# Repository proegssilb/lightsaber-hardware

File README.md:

# lightsaber-hardware
Kicad projects and other files for lightsaber soundboard hardware.

## Caveat Emptor
NO WARRANTY IS AVAILABLE, EXPRESSLY STATED, OR IMPLIED.

These designs and files are not guaranteed to have been reviewed by a professional
engineer. They are not guaranteed to work in your design. They are not even 
guaranteed to work if sent to a PCB manufacturer. The author(s) cannot be held
liable for any injuries or damage that occurs as a result of using these files. It
is your responsibility to review all designs and files carefully before using them 
or integrating them into your own design.

Let the buyer beware.

## Licensing
See the LICENSE.txt file. It's a CERN-OHL-S-2.0 license. If that doesn't work for you,
let's talk.

## Structure
Each subfolder represents a different kicad project, each attempting a different board, 
either in terms of features or formfactor.

Documentation, if any is available, will be either a README in each design's root, or a
`docs/` folder in each design.

## Tool Versions
I use the latest kicad version from flatpak. If you can't open a project, feel free to 
file an issue, but there's a limit to how much support I can provide.

## 3rd Party Services
Preferred PCB manufacturers include JLCBCP, OSH Park, and PCBWay, but any given project 
won't necessarily support all 3 manufacturers. Preferred distributors include Digikey,
Mouser, and LCSC. Same caveat with preferred PCB Manufacturers applies to distributors.

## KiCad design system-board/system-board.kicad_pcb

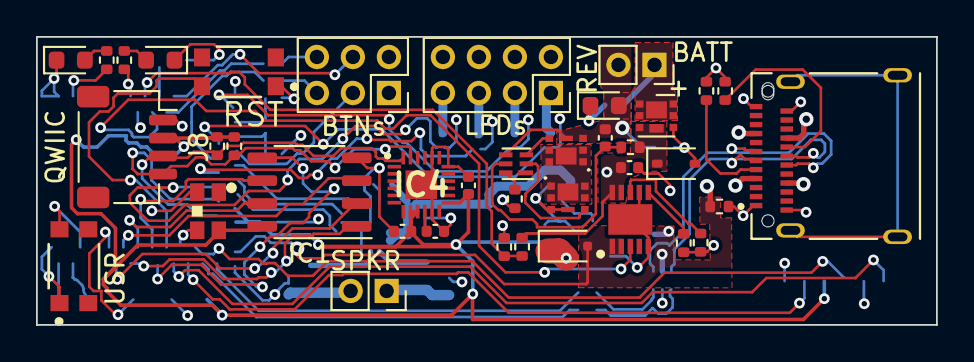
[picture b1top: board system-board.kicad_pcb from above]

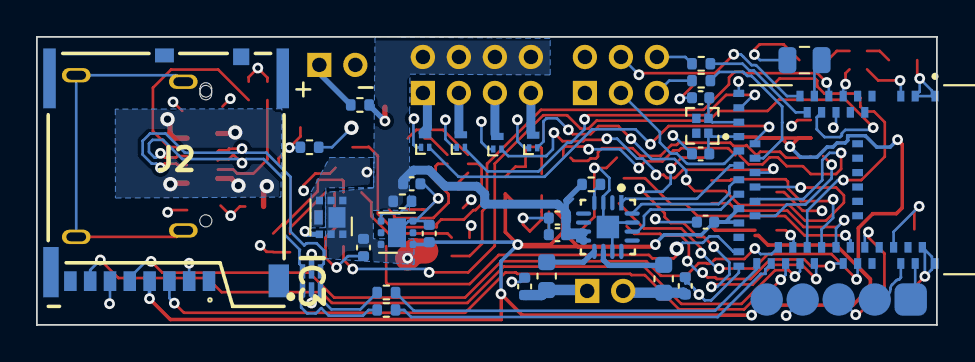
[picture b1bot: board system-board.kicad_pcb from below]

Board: 4 copper layers, 50.0 x 16.0 mm, 72 parts (33 on the bottom side), 74 nets.

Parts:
C1, C7, C9, C13: 10u; C_0402_1005Metric
C2, C3: 22p; C_0402_1005Metric
C4: 0.1 uF; C_0805_2012Metric
C5, C6: 220p; C_0402_1005Metric
C8: 100 nF; C_0402_1005Metric
C10, C14, C15, C16: 0.1 uF; C_0402_1005Metric
C11, C12: 4.7u; C_0402_1005Metric
D1: WS2812B-2020
D2: BLUE; LED_0603_1608Metric
D3: RED; LED_0603_1608Metric
D4: BZX38450; D_SOD-323
D5: REV; LED_0603_1608Metric
D6: PMEG1030EJ; D_SOD-323F
FB1, FB2: FB_Sm; C_0603_1608Metric
IC1: Flash_16Mb; SOP-8_3.9x4.9mm_P1.27mm
IC2: MCP73834T-FCI_MF; SON50P300X300X100-11N-D
IC3: HSP061-2M6; SON50P100X145X65-6N-D
IC4: ICM-20648; QFN40P300X300X95-25N-D
J1: BATT; PinSocket_1x02_P2.00mm_Vertical
J2: 503398-1892; Molex uSD Card Holder Push-Push 503398-1892
J3: DBG; Prog-Pads
J4: SPKR; PinSocket_1x02_P2.00mm_Vertical
J5: LEDs; PinSocket_2x04_P2.00mm_Vertical
J6: BTNs; PinSocket_2x03_P2.00mm_Vertical
J7: 105450-0101; AMPHENOL_12401832E402A
J8: QWIIC; JST_SH_SM04B-SRSS-TB_1x04-1MP_P1.00mm_Horizontal
Q1, Q4: DMP1012UFDF
Q2, Q3: SSM6K504NU.LF; SSM6K504NULF
Q5, Q6, Q7, Q8: PMZB290UNE2YL; Diodes_DFN1006-3
R1, R2: 22; R_0402_1005Metric
R3, R4, R10, R16, R17: 1k; R_0402_1005Metric
R5: 1M; R_0402_1005Metric
R6: 330; R_0402_1005Metric
R7: 2.2k; R_0402_1005Metric
R8, R20, R21: 2.0k; R_0402_1005Metric
R9: 10k; R_0402_1005Metric
R11: 200; R_0402_1005Metric
R12, R13, R14, R15: 100k; R_0402_1005Metric
R18, R19: 5k1; R_0402_1005Metric
SW1: RST; CK_Components-KMR231NG_LFS-MFG
SW2: USR; CK_Components-KMR231NG_LFS-MFG
U1: MDBT50Q-1MV2; XCVR_MDBT50Q-1MV2
U2: MAX98357AETE+T; Maxim_Integrated-T1633-4-0-V-IPC_C
U3: BQ29705DSER; WSON-6_1.5x1.5mm_P0.5mm
U4: TLV75733PDRV; WSON-6-1EP_2x2mm_P0.65mm_EP1x1.6mm
Y1: 32.768k; XTAL_ECS-.327-12.5-1210B-N-TR

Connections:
/A0: J6.3, U1.20 (P0.04/AIN2)
/A1: R17.2, U1.21 (P0.05/AIN3)
/A2: J6.4, U1.14 (P0.30/AIN6)
/A3: R16.2, U1.13 (P0.28/AIN4)
/A4: IC2.3 (STAT1), U1.11 (P0.02/AIN0)
/AREF: C4.2, U1.12 (P0.31/AIN7)
/Blade LED Out/Blade_1_Out: J5.1, Q5.3 (S)
/Blade LED Out/Blade_2_Out: J5.3, Q6.3 (S)
/Blade LED Out/Blade_3_Out: J5.5, Q7.3 (S)
/Blade LED Out/Blade_4_Out: J5.7, Q8.3 (S)
/CONN_USB_D+: IC3.1 (I/O1_1), R2.1
/CONN_USB_D-: IC3.3 (I/O2_1), R1.1
/D5: Q8.2 (G), U1.25 (P1.08)
/D6: Q7.2 (G), U1.23 (TRACECLK/P0.07)
/D9: Q5.2 (G), U1.19 (P0.26)
/D10: Q6.2 (G), U1.16 (P0.27)
/D11: U1.22 (P0.06), U2.1 (DIN)
/D12: U1.24 (P0.08), U2.16 (BCLK)
/D13: U1.26 (TRACEDATA3/P1.09), U2.14 (LRCLK)
/LED1: R4.2, U1.8 (P1.15)
/LED2: R3.2, U1.3 (P1.10)
/MCU_USB_D+: R2.2, U1.35 (D+)
/MCU_USB_D-: R1.2, U1.34 (D-)
/MISO: J2.7 (DAT0), U1.39 (P0.15)
/MOSI: J2.3 (CMD), U1.37 (P0.13)
/NEOPIX: D1.3 (DIN), U1.38 (P0.16)
/Power Management/BATT_FILTERED: C10.1, R6.2, U3.5 (BAT)
/Power Management/BATT_PROT_+: C9.1, D4.1 (K), IC2.9 (VBAT_1), IC2.10 (VBAT_2), Q1.3 (S), Q4.3 (S), R6.1, R12.1
/Power Management/BATT_RAW_+: J1.1, Q1.1 (D), R10.1
/Power Management/BATT_RAW_-: C10.2, D5.2 (A), J1.2, Q3.3 (S), R11.2, U3.4 (VSS)
/Power Management/VBUS: D6.2 (A), IC2.1 (VDD_1), IC2.2 (VDD_2), IC3.5 (VBUS), J7.A4 (VBUS_A), J7.A9 (VBUS_A), J7.B4 (VBUS_B), J7.B9 (VBUS_B), Q4.2 (G), R14.1, U1.32 (VBUS)
/QSPI_CS: IC1.1 (CS#), U1.44 (P0.20)
/QSPI_D0: IC1.5 (SI_(IO0)), U1.41 (P0.17)
/QSPI_D1: IC1.2 (SO_(IO1)), U1.46 (P0.22)
/QSPI_D2: IC1.3 (WP#_(IO2)), U1.45 (P0.23)
/QSPI_D3: IC1.7 (HOLD#_(IO3)), U1.43 (P0.21)
/QSPI_SCK: IC1.6 (SCLK), U1.42 (P0.19)
/RESET: SW1.2, U1.40 (~RESET/P0.18)
/SCK: J2.5 (CLK), U1.36 (P0.14)
/SCL: IC4.23 (SCL_/_SCLK), J8.4, R21.1, U1.27 (TRACEDATA2/P0.11)
/SDA: IC4.24 (SDA_/_SDI), J8.3, R20.2, U1.29 (TRACEDATA1/P0.12)
/SW0: J3.3, U1.47 (TRACEDATA0/P1.00)
/SWCLK: J3.1, U1.53 (SWDCLK)
/SWDIO: J3.2, U1.51 (SWDIO)
/SWITCH: SW2.2, U1.50 (P1.02)
/USB Connector/CC1: J7.A5 (CC1), R18.1
/USB Connector/CC2: J7.B5 (CC2), R19.1
/USB Connector/RAW_D+: IC3.6 (I/O1_2), J7.A6 (D1+), J7.B6 (D2+)
/USB Connector/RAW_D-: IC3.4 (I/O2_2), J7.A7 (D1-), J7.B7 (D2-)
/VDIV: R12.2, R13.1, U1.10 (P0.29/AIN5)
/XL1: C2.1, U1.17 (XL1/P0.00), Y1.2
/XL2: C3.1, U1.18 (XL2/P0.01), Y1.1
/i2s_amp/SOUND_OUT_N: FB1.2, U2.10 (OUTN)
/i2s_amp/SOUND_OUT_P: FB2.2, U2.9 (OUTP)
/i2s_amp/SPKR_N: C5.2, FB1.1, J4.2
/i2s_amp/SPKR_P: C6.2, FB2.1, J4.1
GND: C1.1, C2.2, C3.2, C4.1, C5.1, C6.1, C7.1, C8.2, C9.2, C11.2, C12.2, C13.2, C14.1, C15.2, C16.2, D1.2 (VSS), D2.1 (K), D3.1 (K), IC1.4 (VSS), IC2.5 (VSS), IC2.7 (~PG_(TE)), IC2.11 (EP), IC3.2 (GND), IC4.11 (FSYNC), IC4.18 (GND), IC4.20 (RESV), IC4.25 (EP), J2.2 (CD/DAT3), J2.6 (VSS), J3.4, J6.1, J6.2, J7.A1 (GND_A), J7.A12 (GND_A), J7.B1 (GND_B), J7.B12 (GND_B), J8.1, Q2.3 (S), Q5.1 (D), Q6.1 (D), Q7.1 (D), Q8.1 (D), R7.2, R8.2, R9.2, R13.2, R14.2, R18.2, R19.2, SW1.1, SW2.1, U1.1 (GND), U1.2 (GND), U1.9 (P0.03/AIN1), U1.15 (GND), U1.33 (GND), U1.54 (P0.10/NFC2), U1.55 (GND), U2.3 (GND), U2.11 (GND), U2.15 (GND), U2.17 (EP), U4.3 (GND), U4.7 (GND)
unnamed: D2.2 (A), R3.1
unnamed: D3.2 (A), R4.1
unnamed: D4.2 (A), Q1.2 (G), R11.1
unnamed: D5.1 (K), R10.2
unnamed: IC2.6 (PROG), R8.1
unnamed: IC2.8 (THERM), R9.1
unnamed: C15.1, IC4.10 (REGOUT)
unnamed: J6.5, R17.1
unnamed: J6.6, R16.1
unnamed: Q2.1 (D), Q3.1 (D)
unnamed: Q2.2 (G), U3.2 (Cout)
unnamed: Q3.2 (G), U3.3 (Dout)
unnamed: R5.1, U2.4 (~SD_MODE)
unnamed: R7.1, U3.6 (V-)
unnamed: R15.1, U4.4 (EN)
VCC: C1.2, C12.1, C14.2, C16.1, D1.4 (VDD), IC1.8 (VCC), IC4.8 (VDDIO), IC4.9 (SDO_/_AD0), IC4.13 (VDD), J2.4 (VDD), J3.5, J8.2, R20.1, R21.2, U1.28 (VDD), U1.30 (VDDH), U4.1 (OUT)
VDD: C7.2, C8.1, C11.1, C13.1, D6.1 (K), J5.2, J5.4, J5.6, J5.8, Q4.1 (D), R5.2, R15.2, U2.7 (VDD), U2.8 (VDD), U4.6 (IN)

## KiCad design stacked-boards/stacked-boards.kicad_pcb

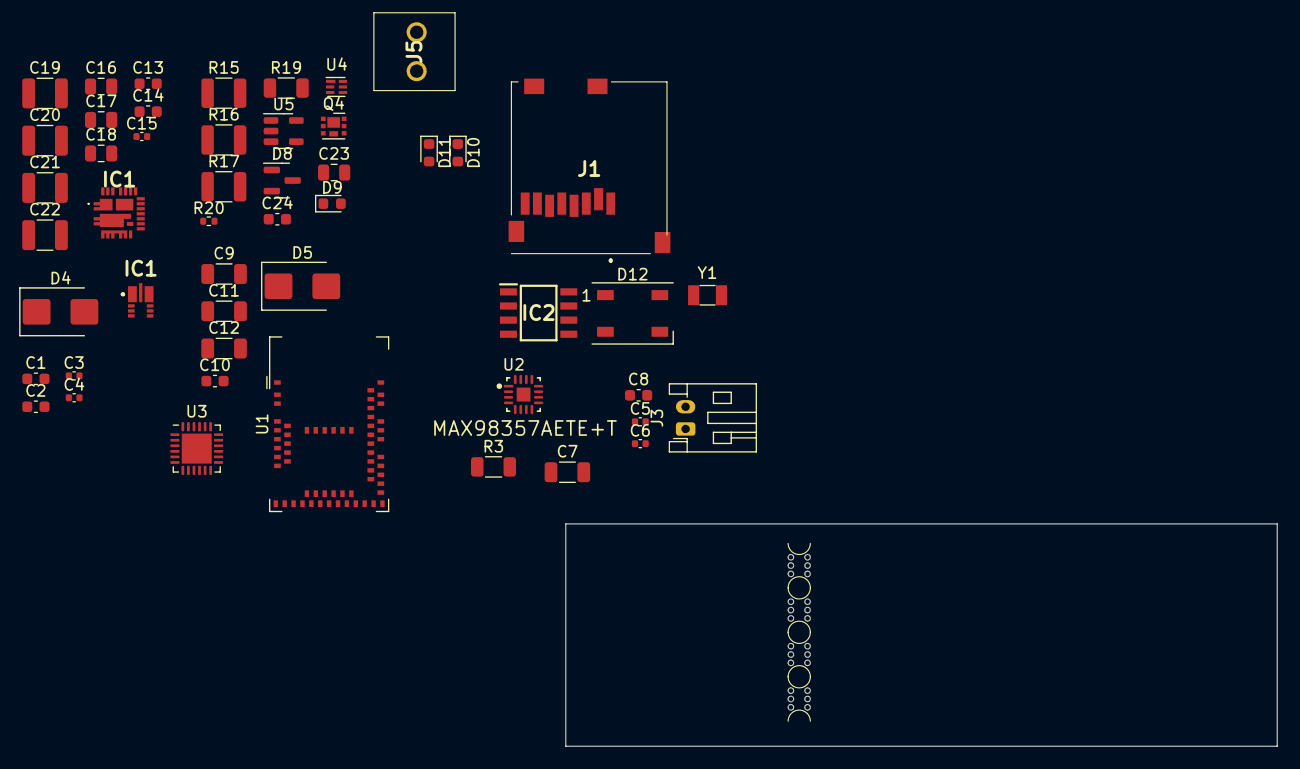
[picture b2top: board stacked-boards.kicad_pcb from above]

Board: 2 copper layers, 64.0 x 20.0 mm, 54 parts (0 on the bottom side), 48 nets, no tracks yet.

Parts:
C1, C2: 10 uF; C_0603_1608Metric
C3, C4: 12 pF; C_0402_1005Metric
C5, C6: 220p; C_0402_1005Metric
C7: 10u; C_1206_3216Metric
C8: 0.1u; C_0603_1608Metric
C9, C11, C12: 1.0 uF; C_1206_3216Metric
C10, C13, C24: 0.1 uF; C_0603_1608Metric
C14: 100 nF; C_0603_1608Metric
C15: 1uF; C_0402_1005Metric
C16, C17: 22 uF; C_0805_2012Metric
C18: 4.7 uF; C_0805_2012Metric
C19: 220 uF; C_1210_3225Metric
C20, C21, C22: 220uF; C_1210_3225Metric
C23: 4.7uF; C_0805_2012Metric
D4, D5: VSSB7L45; D_SMB
D8: BAT54CLT3G; SOT-23
D9, D10: RED; LED_0603_1608Metric
D11: BLUE; LED_0603_1608Metric
D12: WS2812B; LED_WS2812B_PLCC4_5.0x5.0mm_P3.2mm
IC1: SIC437CED-T1-GE3; SIC437CEDT1GE3
IC1#2: AP63357QZV-7; AP63357QZV7
IC2: GD25Q16ETIGR; SOIC127P600X175-8N
J1: Micro_SD_Card; MEM20610118800A
J3: Conn_01x02_Socket; JST_PH_S2B-PH-K_1x02_P2.00mm_Horizontal
J5: Conn_Batt; 15465512
Q4: DMP1012UFDF; Diodes_UDFN2020-6_Type-F
R3: 1M; R_1206_3216Metric
R15: 330; R_1210_3225Metric
R16: 2.2k; R_1210_3225Metric
R17: 380; R_1210_3225Metric
R19: 470; R_1206_3216Metric
R20: 2k; R_0402_1005Metric
U1: MDBT50Q-1MV2; Raytac_MDBT50Q
U2: MAX98357AETE+T; Maxim_Integrated-T1633-4-0-V-IPC_C
U3: STUSB4500QTR; QFN-24-1EP_4x4mm_P0.5mm_EP2.7x2.7mm
U4: BQ29705DSER; WSON-6_1.5x1.5mm_P0.5mm
U5: MCP73831-2-OT; SOT-23-5
Y1: 32.768 kHz; Crystal_SMD_3215-2Pin_3.2x1.5mm
mouse-bite-2mm-slot, mouse-bite-2mm-slot#2, mouse-bite-2mm-slot#3, mouse-bite-2mm-slot#4: VAL**; mouse-bite-2mm-slot

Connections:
+3.3V: C7.2, C8.1, D5.1 (K), D12.1 (VDD), IC2.8 (VCC), J1.P4 (VDD), R3.2, U2.7 (VDD), U2.8 (VDD), U3.22 (VSYS)
+5V: C2.1, C19.1, C20.1, C21.1, C22.1, D4.2 (A), IC1.18 (VOUT), U1.30 (VDDH), U1.32 (VBUS)
/Amp/SPKR_N: C5.2, J3.2
/Amp/SPKR_P: C6.2, J3.1
/LED1: D10.2 (A), U1.8 (P1.15_(LS))
/LED2: D11.2 (A), U1.3 (P1.10_(LS))
/NEOPIX: D12.4 (DIN), U1.38 (P0.16_(HS))
/Power Management/Battery Handling/BATT_PROT_+: C23.1, D8.1 (K), Q4.3 (S), R15.1, U5.3 (V_{BAT})
/Power Management/Battery Handling/BATT_RAW_+: J5.2, Q4.1 (D), R17.1
/Power Management/Battery Handling/BATT_RAW_-: C24.2, D9.2 (A), J5.1, U4.4 (VSS)
/Power Management/Battery Handling/V_CHRG: D4.1 (K), U5.4 (V_{DD})
/Power Management/CHARGING: R19.1, U5.1 (STAT)
/Power Management/PD Negotiation/PD_POW_OUT: C10.1, C14.1, C16.1, C17.1, IC1.1 (VIN_1), IC1.2 (VIN_2), IC1.22 (VIN_3), IC1.26 (VIN_4)
/Power Management/PD Negotiation/USB_CC1: U3.1 (CC1DB), U3.2 (CC1)
/Power Management/PD Negotiation/USB_CC2: U3.4 (CC2), U3.5 (CC2DB)
/Power Management/PD Negotiation/V_USB_PORT: C11.1, U3.24 (VDD)
/QSPI_CS: IC2.1 (CS#), U1.44 (P0.20_(HS))
/QSPI_D0: IC2.5 (SI_(IO0)), U1.41 (P0.17_(HS))
/QSPI_D1: IC2.2 (SO_(IO1)), U1.46 (P0.22/QSPI)
/QSPI_D2: IC2.3 (WP#_(IO2)), U1.45 (P0.23/QSPI)
/QSPI_D3: IC2.7 (HOLD#_(IO3)), U1.43 (P0.21/QSPI)
/QSPI_SCK: IC2.6 (SCLK), U1.42 (P0.19/QSPI_SCK)
Earth: C16.2, C17.2, C18.2, C19.2, C20.2, C21.2, C22.2
GND: C1.1, C2.2, C3.2, C4.2, C5.1, C6.1, C7.1, C8.2, C9.1, C11.2, C12.2, C14.2, C15.2, C23.2, D10.1 (K), D11.1 (K), D12.3 (VSS), IC1.3 (PGND_1), IC1.4 (PGND_2), IC1.13 (PGND_3), IC1.16 (AGND_1), IC1.25 (AGND_2), IC1.27 (PGND_4), IC1.29 (PGND_5), IC1#2.4 (COMP), IC1#2.8 (GND), IC2.4 (VSS), J1.CD1 (CARD_DETECT_1), J1.G1 (GND_1), J1.G2 (GND_2), J1.P1 (DAT2), J1.P6 (VSS), R16.2, R20.2, U1.1 (GND), U1.2 (GND), U1.15 (GND), U1.33 (GND), U1.55 (GND), U2.3 (GND), U2.11 (GND), U2.15 (GND), U2.17 (EP), U3.10 (GND), U3.12 (ADDR0), U3.13 (ADDR1), U3.25 (GND), U5.2 (V_{SS})
I2C_SCL: U1.27 (TRACEDATA2/P0.11), U3.7 (SCL)
I2C_SDA: U1.29 (TRACEDATA1/P0.12), U3.8 (SDA)
MISO/CIPO: J1.P7 (DAT0), U1.39 (P0.15_(HS))
MOSI/COPI: J1.P3 (CMD), U1.37 (P0.13_(HS))
unnamed: C12.1, D5.2 (A), U3.23 (VREG_2V7)
unnamed: D8.2 (A), Q4.2 (G)
unnamed: D9.1 (K), R17.2
unnamed: C13.1, IC1.23 (BOOT)
unnamed: IC1.19 (EN), IC1#2.2 (EN)
unnamed: IC1.17 (FB), IC1#2.3 (FB)
unnamed: IC1.5 (SW_1), IC1.6 (SW_2), IC1.7 (SW_3), IC1.8 (SW_4), IC1.9 (SW_5), IC1.30 (SW_6)
unnamed: C15.1, IC1.15 (VDD)
unnamed: C18.1, IC1.12 (VDRV)
unnamed: C1.2, U1.28 (VDD)
unnamed: C3.1, U1.17 (XL1/P0.00), Y1.2
unnamed: C4.1, U1.18 (XL2/P0.01), Y1.1
unnamed: R3.1, U2.4 (~SD_MODE)
unnamed: C9.2, U3.21 (VREG_1V2)
unnamed: C24.1, R15.2, U4.5 (BAT)
unnamed: R16.1, U4.6 (V-)
unnamed: R20.1, U5.5 (PROG)
SD_CardDetect: J1.CD2 (CARD_DETECT_2), U1.6 (P1.13_(LS))
SD_ChipSel#: J1.P2 (CD/DAT3), U1.7 (P1.14_(LS))
SPI_CLK: J1.P5 (CLK), U1.36 (P0.14_(HS))

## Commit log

2023-06-28 Checkpoint
2023-07-05 Do some calculations, overhaul system-board to be a single board, not a Feather add-on.
2023-07-05 Add most of the missing 3D models, some tweaks
2023-07-05 Add imported footprints & models
2023-07-06 Small tweaks, add a license.
2023-07-07 First attempt
2023-07-10 Redo system-board PCB to use fewer connectors
2023-07-21 Yet another PCB Revision
2023-07-27 Redo design again
